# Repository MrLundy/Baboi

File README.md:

# Baboi
I still have an old printer with a Baboi board, and since efuntime stopped develpment in 2013 I am putting my version here.

I found the version I started with on a forum that isn't there anymore.

https://web.archive.org/web/20160612084530/http://forum.mixshop.com/viewtopic.php?pid=2414

 Reprap firmware based on Sprinter
 Optimize for Sanguinololu 1.2 and above, RAMPS 
 Colin's build V10.1 for Prusa I3 running off of a Baboi Box.
 Chris's modification of Colin's build.

Originally I uploaded version 1.5.5 of my build here.

To compile you will need to use the arduino 1.6.0 DE

Zip file of the latest source:
https://github.com/MrLundy/Baboi/releases

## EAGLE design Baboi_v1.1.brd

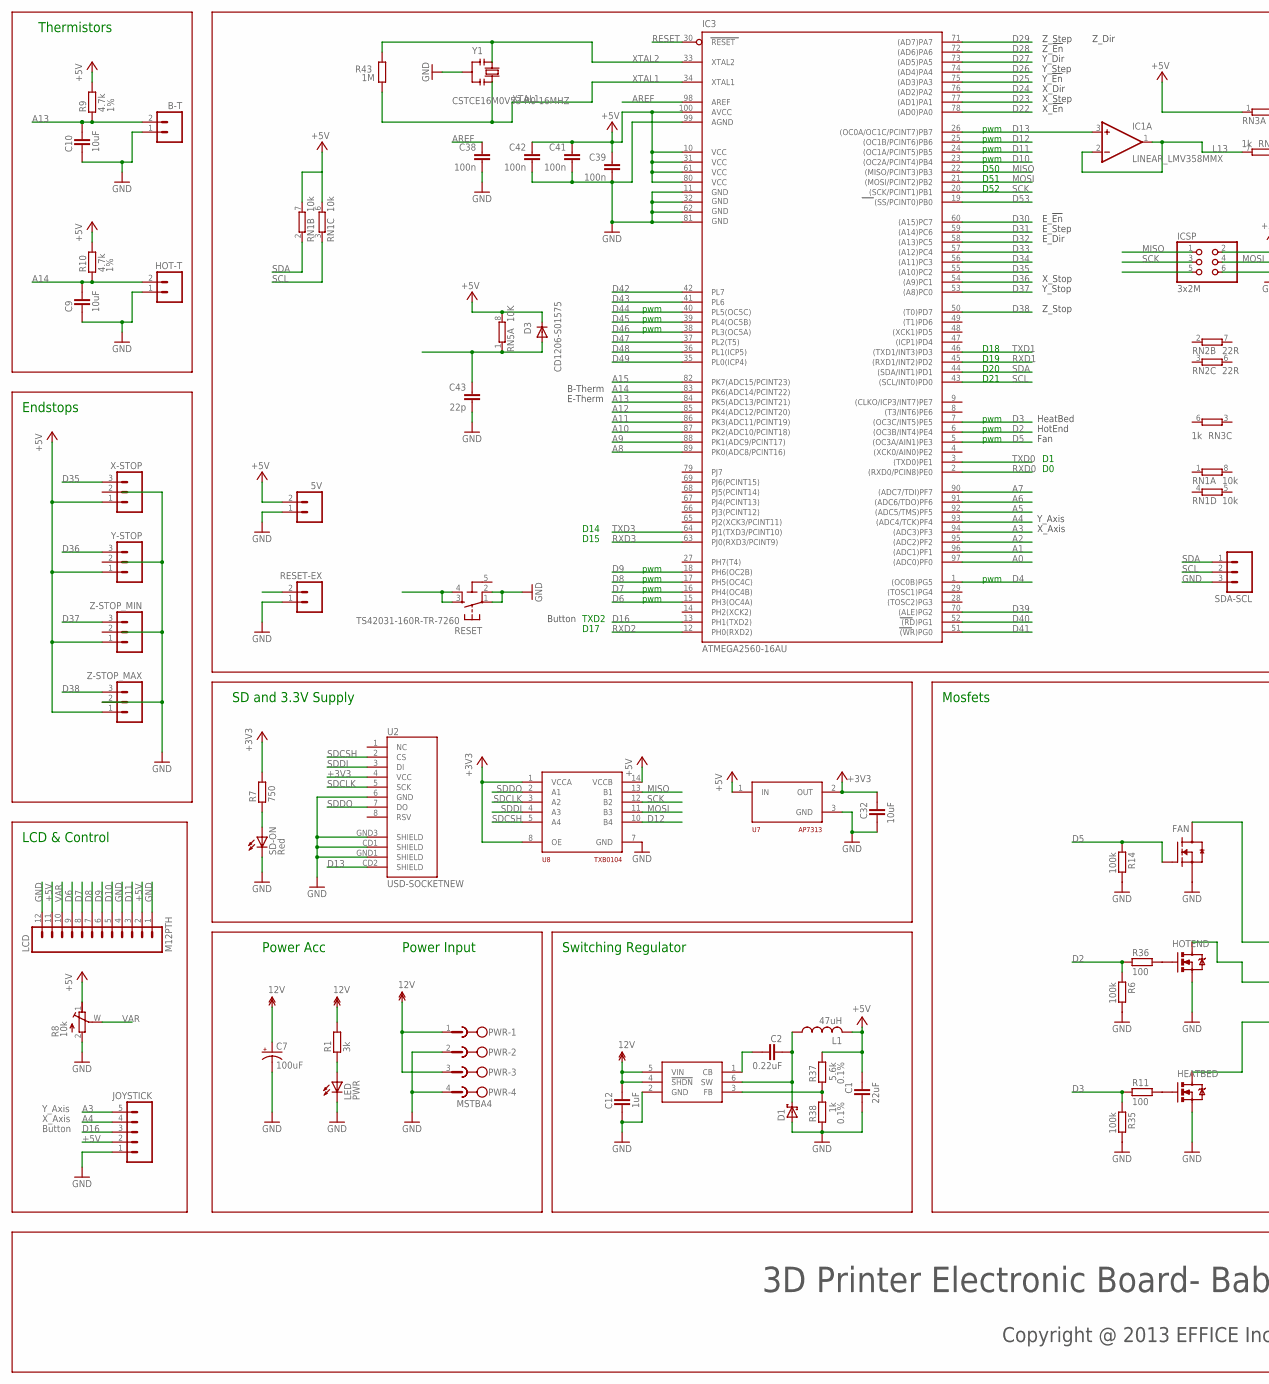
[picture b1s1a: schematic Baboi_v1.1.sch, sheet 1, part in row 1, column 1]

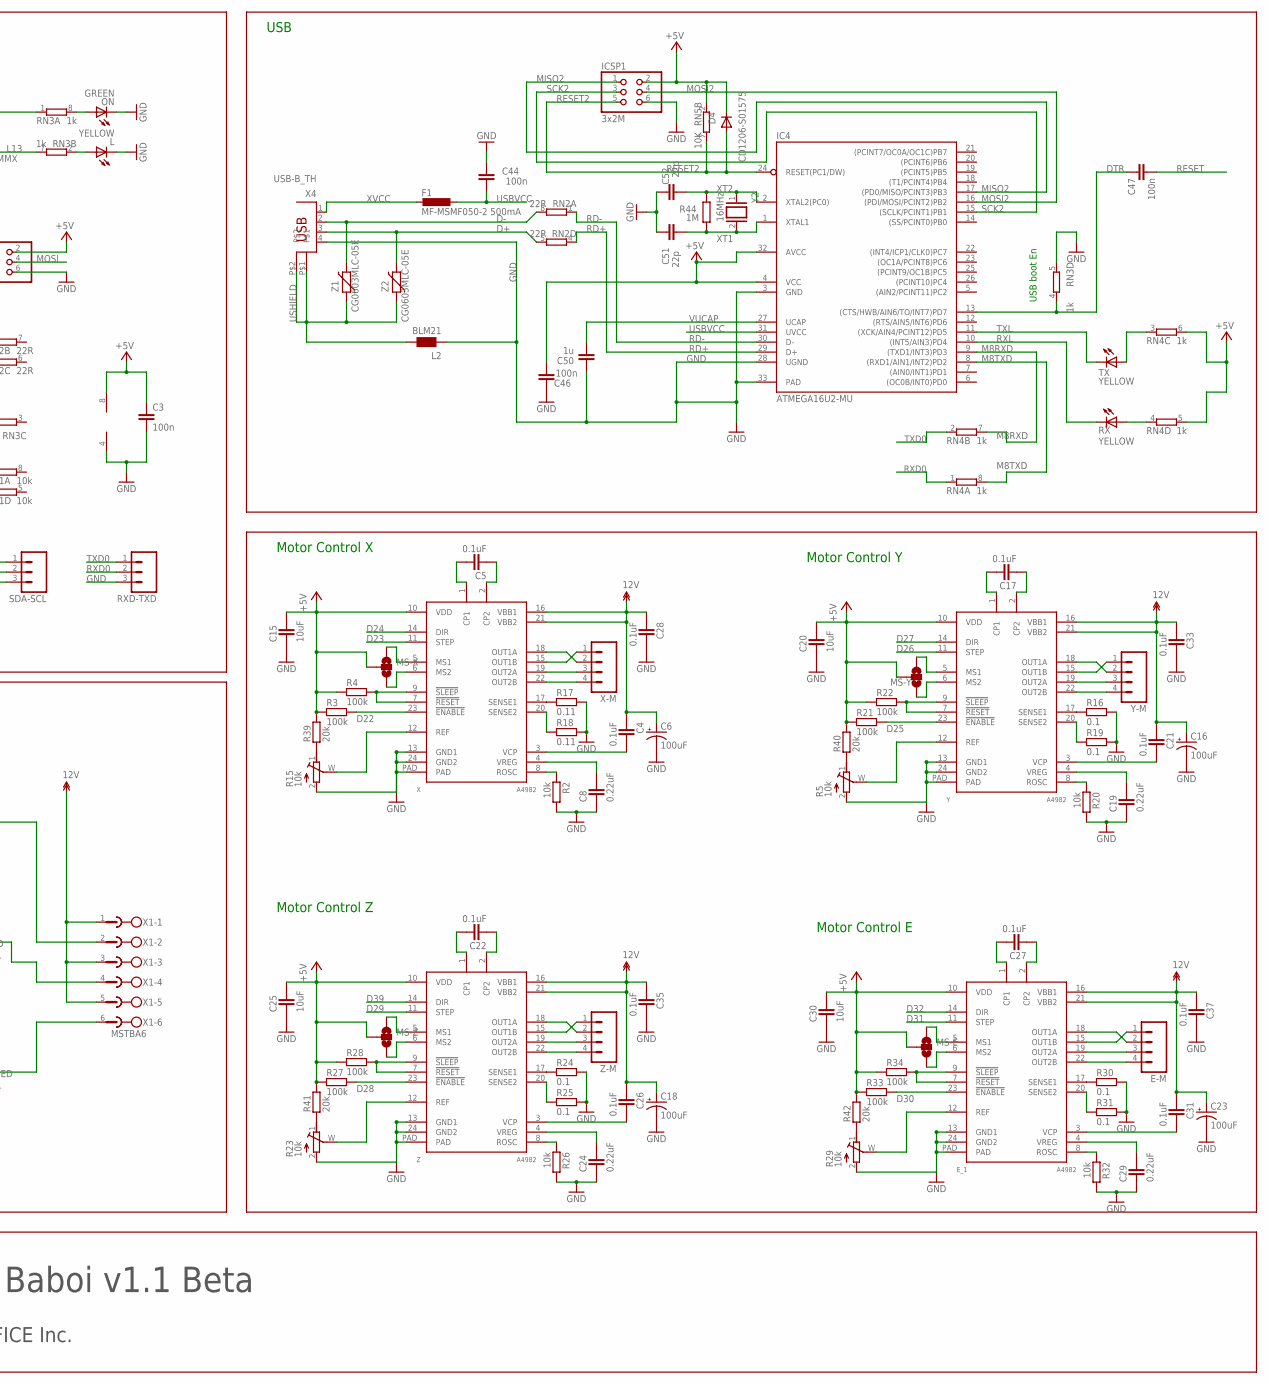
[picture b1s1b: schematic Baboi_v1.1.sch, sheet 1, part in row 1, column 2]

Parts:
5V: M02PTH; 1X02
B-T: M02PTH; 1X02
C1: 22uF; CAPC2012X145AN
C2, C8, C19, C24, C29: 0.22uF; CAPC2012X145AN
C3: 100n; SMARTPRJ_C0603-ROUND
C4, C5, C17, C21, C22, C26, C27, C28, C31, C33, C35, C37: 0.1uF; CAPC2012X145AN
C6, C7, C16, C18, C23: 100uF; PANASONIC_D
C9, C10, C15, C20, C25, C30, C32: 10uF; CAPC2012X145AN
C12: 1uF; CAPC2012X145AN
C38, C39, C41, C42, C44, C46, C47: 100n; C0603-ROUND
C43, C51, C52: 22p; C0603-ROUND
C50: 1u; C0603-ROUND
D1: SCH-DIODESMA; SMA
D3, D4: CD1206-S01575; MINIMELF
E-M: M04PTH; 1X04
E_1: A4982; TSSOP-24
F1: MF-MSMF050-2 500mA; L1812
FAN: RFP30N06LE; SOT95P280X135-3N
HEATBED: RFP30N06LE; TO220V
HOT-T: M02PTH; 1X02
HOTEND: RFP30N06LE; TO220V
IC1: LINEAR_LMV358MMX; LINEAR_MSOP08
IC3: ATMEGA2560-16AU; TQFP100
IC4: ATMEGA16U2-MU; MLF32
ICSP, ICSP1: 3x2M; 2X03
JOYSTICK: M05PTH; 1X05
L: YELLOW; CHIP-LED0805
L1: 47uH; SDR1006
L2: BLM21; 0805
LCD: M12PTH; 1X12
LED: PWR; CHIP-LED0805
MS-E: SOLDERJUMPER_2WAYCONNECTED; SJ_3_CONNECTED
MS-X: SOLDERJUMPER_2WAYCONNECTED; SJ_3_CONNECTED
MS-Y: SOLDERJUMPER_2WAYCONNECTED; SJ_3_CONNECTED
MS-Z: SOLDERJUMPER_2WAYCONNECTED; SJ_3_CONNECTED
ON: GREEN; CHIP-LED0805
PWR: MSTBA4
R1: 3k; RESC2012X70N
R2, R20, R26, R32: 10k; RESC2012X70N
R3, R4, R6, R14, R21, R22, R27, R28, R33, R34, R35: 100k; RESC2012X70N
R5, R8, R15, R23, R29: 10k; RTRIM-ST4ETB
R7: 750; RESC2012X70N
R9, R10: 4.7k; RESC2012X70N; TOLERANCE 1%
R11, R36: 100; RESC2012X70N
R16, R19, R24, R25, R30, R31: 0.1; RESC2012X70N
R17, R18: 0.11; RESC2012X70N
R37: 5.6k; RESC2012X70N; TOLERANCE 0.1%
R38: 1k; RESC2012X70N; TOLERANCE 0.1%
R39, R40, R41, R42: 20k; RESC2012X70N
R43, R44: 1M; R0603-ROUND
RESET: TS42031-160R-TR-7260; TS42
RESET-EX: M02PTH; 1X02
RN1: 10k; RESISTOR-DIL_CAT16
RN2: 22R; CAY16
RN3, RN4: 1k; CAY16
RN5: 10K; CAT16
RX: YELLOW; CHIP-LED0805
RXD-TXD: M03PTH; 1X03
SD-ON: Red; CHIP-LED0805
SDA-SCL: M03PTH; 1X03
TX: YELLOW; CHIP-LED0805
U1: LM2841; TSOT6
U2: USD-SOCKETNEW; MICRO-SD-SOCKET-PP
U7: AP7313; SOT23C
U8: TXB0104; TSSOP14
X: A4982; TSSOP-24
X1: MSTBA6
X4: USB-B_TH; PN61729
X-M: M04PTH; 1X04
X-STOP: M03PTH; 1X03
Y: A4982; TSSOP-24
Y1: CSTCE16M0V53-R0 16MHZ; RESONATOR
Y2: 16MHz; QS
Y-M: M04PTH; 1X04
Y-STOP: M03PTH; 1X03
Z: A4982; TSSOP-24
Z1, Z2: CG0603MLC-05E; CT/CN0603
Z-M: M04PTH; 1X04
Z-STOP_MAX: M03PTH; 1X03
Z-STOP_MIN: M03PTH; 1X03

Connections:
5-GND: RESET.5 (5-GND)
12V: C4.1, C6.+, C7.+, C12.1, C16.+, C18.+, C21.1, C23.+, C26.1, C28.1, C31.1, C33.1, C35.1, C37.1, E_1.16 (VBB1), E_1.21 (VBB2), PWR.1, PWR.3, R1.2, U1.4 (!SHDN), U1.5 (VIN), X.16 (VBB1), X.21 (VBB2), X1.1, X1.3, X1.5, Y.16 (VBB1), Y.21 (VBB2), Z.16 (VBB1), Z.21 (VBB2)
+3V3: C32.1, R7.2, U2.4 (VCC), U7.2 (OUT), U8.1 (VCCA), U8.8 (OE)
+5V: 5V.2, C1.1, C3.1, C15.2, C20.2, C25.2, C30.2, C39.1, C41.1, C42.1, C46.1, D3.C, D4.C, E_1.10 (VDD), IC1.8 (V+), IC3.10 (VCC), IC3.31 (VCC1), IC3.61 (VCC2), IC3.80 (VCC3), IC3.100 (AVCC), IC4.4 (VCC), IC4.32 (AVCC), ICSP.2, ICSP1.2, JOYSTICK.2, L1.P$2 (2), LCD.2, LCD.11, MS-E.2, MS-X.2, MS-Y.2, MS-Z.2, R3.1, R4.1, R8.1 (A), R9.2, R10.2, R21.1, R22.1, R27.1, R28.1, R33.1, R34.1, R37.1, R39.2, R40.2, R41.2, R42.2, RN1.6 (2), RN1.7 (2), RN3.1, RN4.5 (2), RN4.6 (2), RN5.2 (1), RN5.8 (2), U7.1 (IN), U8.14 (VCCB), X.10 (VDD), X-STOP.1, Y.10 (VDD), Y-STOP.1, Z.10 (VDD), Z-STOP_MAX.1, Z-STOP_MIN.1
A0: IC3.97 ((ADC0)PF0)
A1: IC3.96 ((ADC1)PF1)
A2: IC3.95 ((ADC2)PF2)
A3: IC3.94 ((ADC3)PF3), JOYSTICK.5
A4: IC3.93 ((ADC4/TCK)PF4), JOYSTICK.4
A5: IC3.92 ((ADC5/TMS)PF5)
A6: IC3.91 ((ADC6/TDO)PF6)
A7: IC3.90 ((ADC7/TDI)PF7)
A8: IC3.89 (PK0(ADC8/PCINT16))
A9: IC3.88 (PK1(ADC9/PCINT17))
A10: IC3.87 (PK2(ADC10/PCINT18))
A11: IC3.86 (PK3(ADC11/PCINT19))
A12: IC3.85 (PK4(ADC12/PCINT20))
A13: B-T.2, C10.2, IC3.84 (PK5(ADC13/PCINT21)), R9.1
A14: C9.2, HOT-T.2, IC3.83 (PK6(ADC14/PCINT22)), R10.1
A15: IC3.82 (PK7(ADC15/PCINT23))
AREF: C38.1, IC3.98 (AREF)
D2: IC3.6 ((OC3B/INT4)PE4), R6.1, R36.1
D3: IC3.7 ((OC3C/INT5)PE5), R11.1, R35.1
D4: IC3.1 ((OC0B)PG5)
D5: FAN.1 (G), IC3.5 ((OC3A/AIN1)PE3), R14.1
D6: IC3.15 (PH3(OC4A)), LCD.9
D7: IC3.16 (PH4(OC4B)), LCD.8
D8: IC3.17 (PH5(OC4C)), LCD.7
D9: IC3.18 (PH6(OC2B)), LCD.6
D10: IC3.23 ((OC2A/PCINT4)PB4), LCD.5
D11: IC3.24 ((OC1A/PCINT5)PB5), LCD.3
D12: IC3.25 ((OC1B/PCINT6)PB6), U8.10 (B4)
D13: IC1.3 (+IN), IC3.26 ((OC0A/OC1C/PCINT7)PB7), U2.CD2 (SHIELD)
D16: IC3.13 (PH1(TXD2)), JOYSTICK.3
D22: IC3.78 ((AD0)PA0), R3.2, X.23 (!ENABLE)
D23: IC3.77 ((AD1)PA1), X.11 (STEP)
D24: IC3.76 ((AD2)PA2), X.14 (DIR)
D25: IC3.75 ((AD3)PA3), R21.2, Y.23 (!ENABLE)
D26: IC3.74 ((AD4)PA4), Y.11 (STEP)
D27: IC3.73 ((AD5)PA5), Y.14 (DIR)
D28: IC3.72 ((AD6)PA6), R27.2, Z.23 (!ENABLE)
D29: IC3.71 ((AD7)PA7), Z.11 (STEP)
D30: E_1.23 (!ENABLE), IC3.60 ((A15)PC7), R33.2
D31: E_1.11 (STEP), IC3.59 ((A14)PC6)
D32: E_1.14 (DIR), IC3.58 ((A13)PC5)
D33: IC3.57 ((A12)PC4)
D34: IC3.56 ((A11)PC3)
D35: IC3.55 ((A10)PC2), X-STOP.3
D36: IC3.54 ((A9)PC1), Y-STOP.3
D37: IC3.53 ((A8)PC0), Z-STOP_MIN.3
D38: IC3.50 ((T0)PD7), Z-STOP_MAX.3
D39: IC3.70 ((ALE)PG2), Z.14 (DIR)
D40: IC3.52 ((RD)PG1)
D41: IC3.51 ((WR)PG0)
D42: IC3.42 (PL7)
D43: IC3.41 (PL6)
D44: IC3.40 (PL5(OC5C))
D45: IC3.39 (PL4(OC5B))
D46: IC3.38 (PL3(OC5A))
D47: IC3.37 (PL2(T5))
D48: IC3.36 (PL1(ICP5))
D49: IC3.35 (PL0(ICP4))
D53: IC3.19 ((SS/PCINT0)PB0)
D+: RN2.5 (2), X4.3, Z2.2
D-: RN2.8 (2), X4.2, Z1.2
DTR: C47.1, IC4.13 ((CTS/HWB/AIN6/TO/INT7)PD7), RN3.4 (1)
FAN: FAN.3 (D), X1.2
GND: 5V.1, B-T.1, C1.2, C3.2, C6.-, C7.-, C8.1, C9.1, C10.1, C12.2, C15.1, C16.-, C18.-, C19.1, C20.1, C23.-, C24.1, C25.1, C28.2, C29.1, C30.1, C32.2, C33.2, C35.2, C37.2, C38.2, C39.2, C41.2, C42.2, C43.2, C44.2, C46.2, C50.2, C51.2, C52.2, D1.A, E_1.13 (GND1), E_1.24 (GND2), E_1.PAD, FAN.2 (S), HEATBED.3 (S), HOT-T.1, HOTEND.3 (S), IC1.4 (V-), IC3.11 (GND), IC3.32 (GND1), IC3.62 (GND2), IC3.81 (GND3), IC3.99 (AGND), IC4.3 (GND), IC4.28 (UGND), IC4.33 (PAD), ICSP.6, ICSP1.6, JOYSTICK.1, L.C, L2.1, LCD.1, LCD.4, LCD.12, LED.C, ON.C, PWR.2, PWR.4, R2.2, R5.2 (E), R6.2, R8.2 (E), R14.2, R15.2 (E), R16.2, R17.2, R18.2, R19.2, R20.2, R23.2 (E), R24.2, R25.2, R26.2, R29.2 (E), R30.2, R31.2, R32.2, R35.2, R38.2, RESET.1, RESET.2, RESET-EX.1, RN3.5 (2), RXD-TXD.3, SD-ON.C, SDA-SCL.3, U1.2 (GND), U2.6 (GND), U2.CD1 (SHIELD), U2.GND1 (SHIELD), U2.GND3 (SHIELD), U7.3 (GND), U8.7 (GND), X.13 (GND1), X.24 (GND2), X.PAD, X4.4, Y.13 (GND1), Y.24 (GND2), Y.PAD, Y1.2, Z.13 (GND1), Z.24 (GND2), Z.PAD, Z-STOP_MAX.2
HOTBED-GND: HEATBED.2 (D), X1.6
HOTEND-GND: HOTEND.2 (D), X1.4
L13: IC1.1 (OUT), IC1.2 (-IN), RN3.7 (2)
M8RXD: IC4.9 ((TXD1/INT3)PD3), RN4.7 (2)
M8TXD: IC4.8 ((RXD1/AIN1/INT2)PD2), RN4.8 (2)
MISO: IC3.22 ((MISO/PCINT3)PB3), ICSP.1, U8.13 (B1)
MISO2: IC4.17 ((PD0/MISO/PCINT3)PB3), ICSP1.1
MOSI: IC3.21 ((MOSI/PCINT2)PB2), ICSP.4, U8.11 (B3)
MOSI2: IC4.16 ((PDI/MOSI/PCINT2)PB2), ICSP1.4
unnamed: LED.A, R1.1
unnamed: R7.1, SD-ON.A
unnamed: X.19 (OUT2A), X-M.3
unnamed: X.22 (OUT2B), X-M.4
unnamed: Y.19 (OUT2A), Y-M.3
unnamed: Y.22 (OUT2B), Y-M.4
unnamed: HEATBED.1 (G), R11.2
unnamed: R5.1 (A), R40.1
unnamed: Z.19 (OUT2A), Z-M.3
unnamed: X.18 (OUT1A), X-M.2
unnamed: C5.2, X.1 (CP1)
unnamed: C5.1, X.2 (CP2)
unnamed: R2.1, X.8 (ROSC)
unnamed: R17.1, X.17 (SENSE1)
unnamed: R18.1, X.20 (SENSE2)
unnamed: C4.2, X.3 (VCP)
unnamed: X.15 (OUT1B), X-M.1
unnamed: R15.W (S), X.12 (REF)
unnamed: C8.2, X.4 (VREG)
unnamed: Z.22 (OUT2B), Z-M.4
unnamed: R4.2, X.7 (!RESET), X.9 (!SLEEP)
unnamed: R37.2, R38.1, U1.3 (FB)
unnamed: E-M.3, E_1.19 (OUT2A)
unnamed: E-M.4, E_1.22 (OUT2B)
unnamed: Y.15 (OUT1B), Y-M.1
unnamed: MS-X.1, X.5 (MS1)
unnamed: MS-X.3, X.6 (MS2)
unnamed: C17.2, Y.1 (CP1)
unnamed: C17.1, Y.2 (CP2)
unnamed: Y.18 (OUT1A), Y-M.2
unnamed: R19.1, Y.20 (SENSE2)
unnamed: R5.W (S), Y.12 (REF)
unnamed: R20.1, Y.8 (ROSC)
unnamed: C19.2, Y.4 (VREG)
unnamed: R22.2, Y.7 (!RESET), Y.9 (!SLEEP)
unnamed: C21.2, Y.3 (VCP)
unnamed: R16.1, Y.17 (SENSE1)
unnamed: Z.15 (OUT1B), Z-M.1
unnamed: Z.18 (OUT1A), Z-M.2
unnamed: MS-Y.1, Y.5 (MS1)
unnamed: MS-Y.3, Y.6 (MS2)
unnamed: C22.2, Z.1 (CP1)
unnamed: C22.1, Z.2 (CP2)
unnamed: R24.1, Z.17 (SENSE1)
unnamed: R25.1, Z.20 (SENSE2)
unnamed: R23.W (S), Z.12 (REF)
unnamed: R26.1, Z.8 (ROSC)
unnamed: C24.2, Z.4 (VREG)
unnamed: R28.2, Z.7 (!RESET), Z.9 (!SLEEP)
unnamed: C26.2, Z.3 (VCP)
unnamed: E-M.1, E_1.15 (OUT1B)
unnamed: E-M.2, E_1.18 (OUT1A)
unnamed: MS-Z.1, Z.5 (MS1)
unnamed: MS-Z.3, Z.6 (MS2)
unnamed: C27.2, E_1.1 (CP1)
unnamed: C27.1, E_1.2 (CP2)
unnamed: E_1.17 (SENSE1), R30.1
unnamed: E_1.20 (SENSE2), R31.1
unnamed: E_1.12 (REF), R29.W (S)
unnamed: E_1.8 (ROSC), R32.1
unnamed: C29.2, E_1.4 (VREG)
unnamed: E_1.7 (!RESET), E_1.9 (!SLEEP), R34.2
unnamed: C31.2, E_1.3 (VCP)
unnamed: RESET.3, RESET.4
unnamed: R15.1 (A), R39.1
unnamed: ON.A, RN3.8 (2)
unnamed: HOTEND.1 (G), R36.2
unnamed: E_1.5 (MS1), MS-E.1
unnamed: E_1.6 (MS2), MS-E.3
unnamed: R29.1 (A), R42.1
unnamed: C2.1, D1.C, L1.P$1 (1), U1.6 (SW)
unnamed: RN4.4 (1), RX.A
unnamed: C2.2, U1.1 (CB)
unnamed: R23.1 (A), R41.1
unnamed: RN4.3 (1), TX.A
unnamed: L.A, RN3.2 (1)
unnamed: C43.1, D3.A, RN5.1
RD+: IC4.29 (D+), RN2.4 (1)
RD-: IC4.30 (D-), RN2.1
RESET: C47.2, IC3.30 (RESET)
RESET2: D4.A, IC4.24 (RESET(PC1/DW)), ICSP1.5, RN5.7 (2)
RXD0: IC3.2 ((RXD0/PCIN8)PE0), RN4.1, RXD-TXD.2
RXD1: IC3.45 ((RXD1/INT2)PD2)
RXD2: IC3.12 (PH0(RXD2))
RXD3: IC3.63 (PJ0(RXD3/PCINT9))
RXL: IC4.10 ((INT5/AIN3)PD4), RX.C
SCK: IC3.20 ((SCK/PCINT1)PB1), ICSP.3, U8.12 (B2)
SCK2: IC4.15 ((SCLK/PCINT1)PB1), ICSP1.3
SCL: IC3.43 ((SCL/INT0)PD0), RN1.3 (1), SDA-SCL.2
SDA: IC3.44 ((SDA/INT1)PD1), RN1.2 (1), SDA-SCL.1
SDCLK: U2.5 (SCK), U8.3 (A2)
SDCSH: U2.2 (CS), U8.5 (A4)
SDDI: U2.3 (DI), U8.4 (A3)
SDDO: U2.7 (DO), U8.2 (A1)
TXD0: IC3.3 ((TXD0)PE1), RN4.2 (1), RXD-TXD.1
TXD1: IC3.46 ((TXD1/INT3)PD3)
TXD3: IC3.64 (PJ1(TXD3/PCINT10))
TXL: IC4.11 ((XCK/AIN4/PCINT12)PD5), TX.C
USBVCC: C44.1, F1.1, IC4.31 (UVCC)
USHIELD: L2.2, X4.P$1, X4.P$2, Z1.1, Z2.1
VAR: LCD.10, R8.W (S)
VUCAP: C50.1, IC4.27 (UCAP)
XT1: C51.1, IC4.1 (XTAL1), R44.1, Y2.2
XT2: C52.1, IC4.2 (XTAL2(PC0)), R44.2, Y2.1
XTAL1: IC3.34 (XTAL1), R43.1, Y1.3
XTAL2: IC3.33 (XTAL2), R43.2, Y1.1
XVCC: F1.2, X4.1

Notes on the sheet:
Power Acc
Power Input
Switching Regulator
pwm
X_Dir
X_Step
X_!En
Y_Dir
Y_Step
Y_!En
Z_Dir
Z_Step
Z_!En
E_Dir
E_Step
E_!En
E-Therm
B-Therm
Y_Axis
X_Axis
Button
Fan
HotEnd
HeatBed
X_Stop
Y_Stop
Z_Stop
D50
D51
D52
USB boot En
Motor Control X
Motor Control Y
Motor Control Z
Motor Control E
Thermistors
SD and 3.3V Supply
Mosfets
Endstops
USB

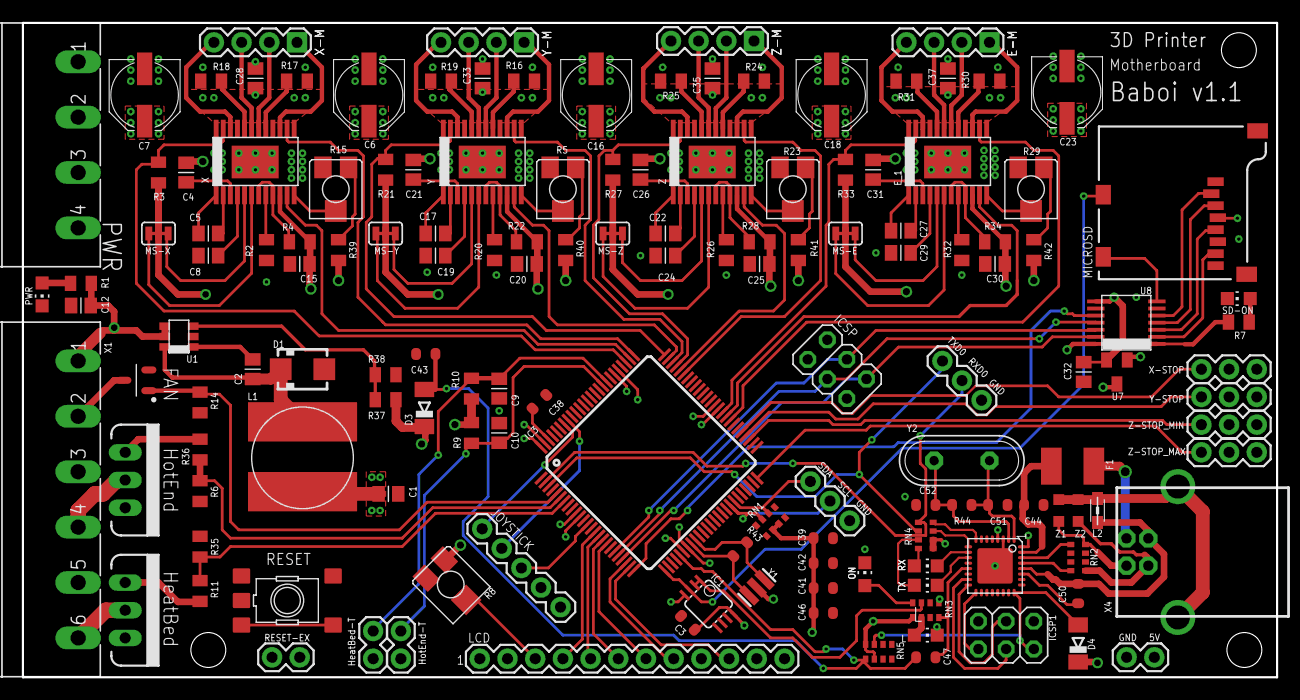
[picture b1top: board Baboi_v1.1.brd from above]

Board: 4 copper layers, 115.0 x 60.0 mm, 146 parts (0 on the bottom side), 152 nets.

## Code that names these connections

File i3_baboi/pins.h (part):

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*
*                  ATMega168
*                   +-\/-+
*             PC6  1|    |28  PC5 (AI 5 / D19)
*       (D 0) PD0  2|    |27  PC4 (AI 4 / D18)
*       (D 1) PD1  3|    |26  PC3 (AI 3 / D17)
*       (D 2) PD2  4|    |25  PC2 (AI 2 / D16)
*  PWM+ (D 3) PD3  5|    |24  PC1 (AI 1 / D15)
*       (D 4) PD4  6|    |23  PC0 (AI 0 / D14)
*             VCC  7|    |22  GND
*             GND  8|    |21  AREF
*             PB6  9|    |20  AVCC
*             PB7 10|    |19  PB5 (D 13)
*  PWM+ (D 5) PD5 11|    |18  PB4 (D 12)
*  PWM+ (D 6) PD6 12|    |17  PB3 (D 11) PWM
*       (D 7) PD7 13|    |16  PB2 (D 10) PWM
*       (D 8) PB0 14|    |15  PB1 (D 9)  PWM
*                   +----+
****************************************************************************************/
#if MOTHERBOARD == 0
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#define SDPOWER          -1
#define SDSS          -1
#define LED_PIN            -1
#define FAN_PIN            -1
#define PS_ON_PIN          15
#define KILL_PIN           -1
#define ALARM_PIN          -1
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*                        ATMega644P
*
*                        +---\/---+
*            (D 0) PB0  1|        |40  PA0 (AI 0 / D31)
*            (D 1) PB1  2|        |39  PA1 (AI 1 / D30)
*       INT2 (D 2) PB2  3|        |38  PA2 (AI 2 / D29)
*        PWM (D 3) PB3  4|        |37  PA3 (AI 3 / D28)
*        PWM (D 4) PB4  5|        |36  PA4 (AI 4 / D27)
*       MOSI (D 5) PB5  6|        |35  PA5 (AI 5 / D26)
*       MISO (D 6) PB6  7|        |34  PA6 (AI 6 / D25)
*        SCK (D 7) PB7  8|        |33  PA7 (AI 7 / D24)
*                  RST  9|        |32  AREF
*                  VCC 10|        |31  GND 
*                  GND 11|        |30  AVCC
*                XTAL2 12|        |29  PC7 (D 23)
*                XTAL1 13|        |28  PC6 (D 22)
*       RX0 (D 8)  PD0 14|        |27  PC5 (D 21) TDI
*       TX0 (D 9)  PD1 15|        |26  PC4 (D 20) TDO
*  INT0 RX1 (D 10) PD2 16|        |25  PC3 (D 19) TMS
*  INT1 TX1 (D 11) PD3 17|        |24  PC2 (D 18) TCK
*       PWM (D 12) PD4 18|        |23  PC1 (D 17) SDA
*       PWM (D 13) PD5 19|        |22  PC0 (D 16) SCL
*       PWM (D 14) PD6 20|        |21  PD7 (D 15) PWM
*                        +--------+
*
****************************************************************************************/
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#define SDPOWER          -1
#define SDSS          -1
#define LED_PIN             0
#define FAN_PIN            -1
#define PS_ON_PIN          -1
#define KILL_PIN           -1
#define ALARM_PIN          -1
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//pin for controlling the PSU.
#define PS_ON_PIN       14

#define FAN_PIN         -1
#define KILL_PIN        -1
#define ALARM_PIN          -1

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#define SDSS		  4

#define SDPOWER          -1
#define FAN_PIN          -1
#define TEMP_0_PIN        0
#define TEMP_1_PIN        5
#define LED_PIN          -1
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#define HEATER_0_PIN 16
#define TEMP_0_PIN 0

#define FAN_PIN -1

//bed pins
#define HEATER_1_PIN -1
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#define SDSS		  4

#define SDPOWER          -1
#define FAN_PIN          -1
#define TEMP_0_PIN        0
#define TEMP_1_PIN        5
#define LED_PIN          -1
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#define SDPOWER            -1
#define SDSS               53
#define LED_PIN            -1
#define FAN_PIN            5
#define PS_ON_PIN          12
#define KILL_PIN           -1
#define ALARM_PIN          -1
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#ifdef RAMPS_V_1_0 // RAMPS_V_1_0
  #define HEATER_0_PIN     12    // RAMPS 1.0
  #define HEATER_1_PIN     -1    // RAMPS 1.0
  #define FAN_PIN          11    // RAMPS 1.0

#else // RAMPS_V_1_1 or RAMPS_V_1_2
  #define HEATER_0_PIN     10    // RAMPS 1.1
  #define HEATER_1_PIN      8    // RAMPS 1.1
  #define FAN_PIN           9    // RAMPS 1.1
#endif

#define TEMP_0_PIN          2    // MUST USE ANALOG INPUT NUMBERING NOT DIGITAL OUTPUT NUMBERING!
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#define SDPOWER          -1
#define SDSS          -1
#define LED_PIN            -1
#define FAN_PIN             5
#define PS_ON_PIN          -1
#define KILL_PIN           -1
#define ALARM_PIN          -1
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    #define SDSS          17
    #define LED_PIN         -1    //changed @ rkoeppl 20110410
    #define TEMP_1_PIN      -1    //changed @ rkoeppl 20110410
    #define FAN_PIN         -1    //changed @ rkoeppl 20110410
    #define PS_ON_PIN       -1    //changed @ rkoeppl 20110410
    //our pin for debugging.
    
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
#define LED_PIN            -1

#define FAN_PIN            -1 

#define PS_ON_PIN          -1
#define KILL_PIN           -1
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    #define SDSS            -1
    #define LED_PIN         -1    
    #define TEMP_1_PIN      2    //Bed   
    #define FAN_PIN         -1    
    #define PS_ON_PIN       15    

#endif
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
#define HEATER_0_PIN       15  // Extruder
#define HEATER_1_PIN       14  // Bed
#define FAN_PIN            16  // Fan   

#define TEMP_0_PIN          7  // Extruder
#define TEMP_1_PIN          6  // Bed
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
#define HEATER_0_PIN       15  // Extruder
#define HEATER_1_PIN       14  // Bed
#define FAN_PIN            16  // Fan

#define TEMP_0_PIN          1  // Extruder
#define TEMP_1_PIN          0  // Bed
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
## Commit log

2020-10-27 Including older versions of the firmware
    Colin's v10.1 right up to my v1.5.5
2020-10-27 Delete .DS_Store
    Don't need this on here.
2020-10-27 Added Original Schematics
2020-10-27 Update README.md
    added arduino 1.6.0 note
2021-01-25 tuning PIDs for stable hotend. Was unable to reach stable temp without sock and failsafing off.
2021-01-27 after replacing corrupted files, and tuning PIDs
2022-06-02 Update i3_baboi.ino
    Added M18 (turn motors off) because octoprint doesn't use M84.
2022-08-30 Update Configuration.h
    shortened homing position from y225 to y220 to avoid crashing at y<5mm.

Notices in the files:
Baboi_v1.1.brd:
GPL
Copyright @ 2013  - efuntime.com
Baboi_v1.1.sch:
Copyright @ 2013 EFFICE Inc.
